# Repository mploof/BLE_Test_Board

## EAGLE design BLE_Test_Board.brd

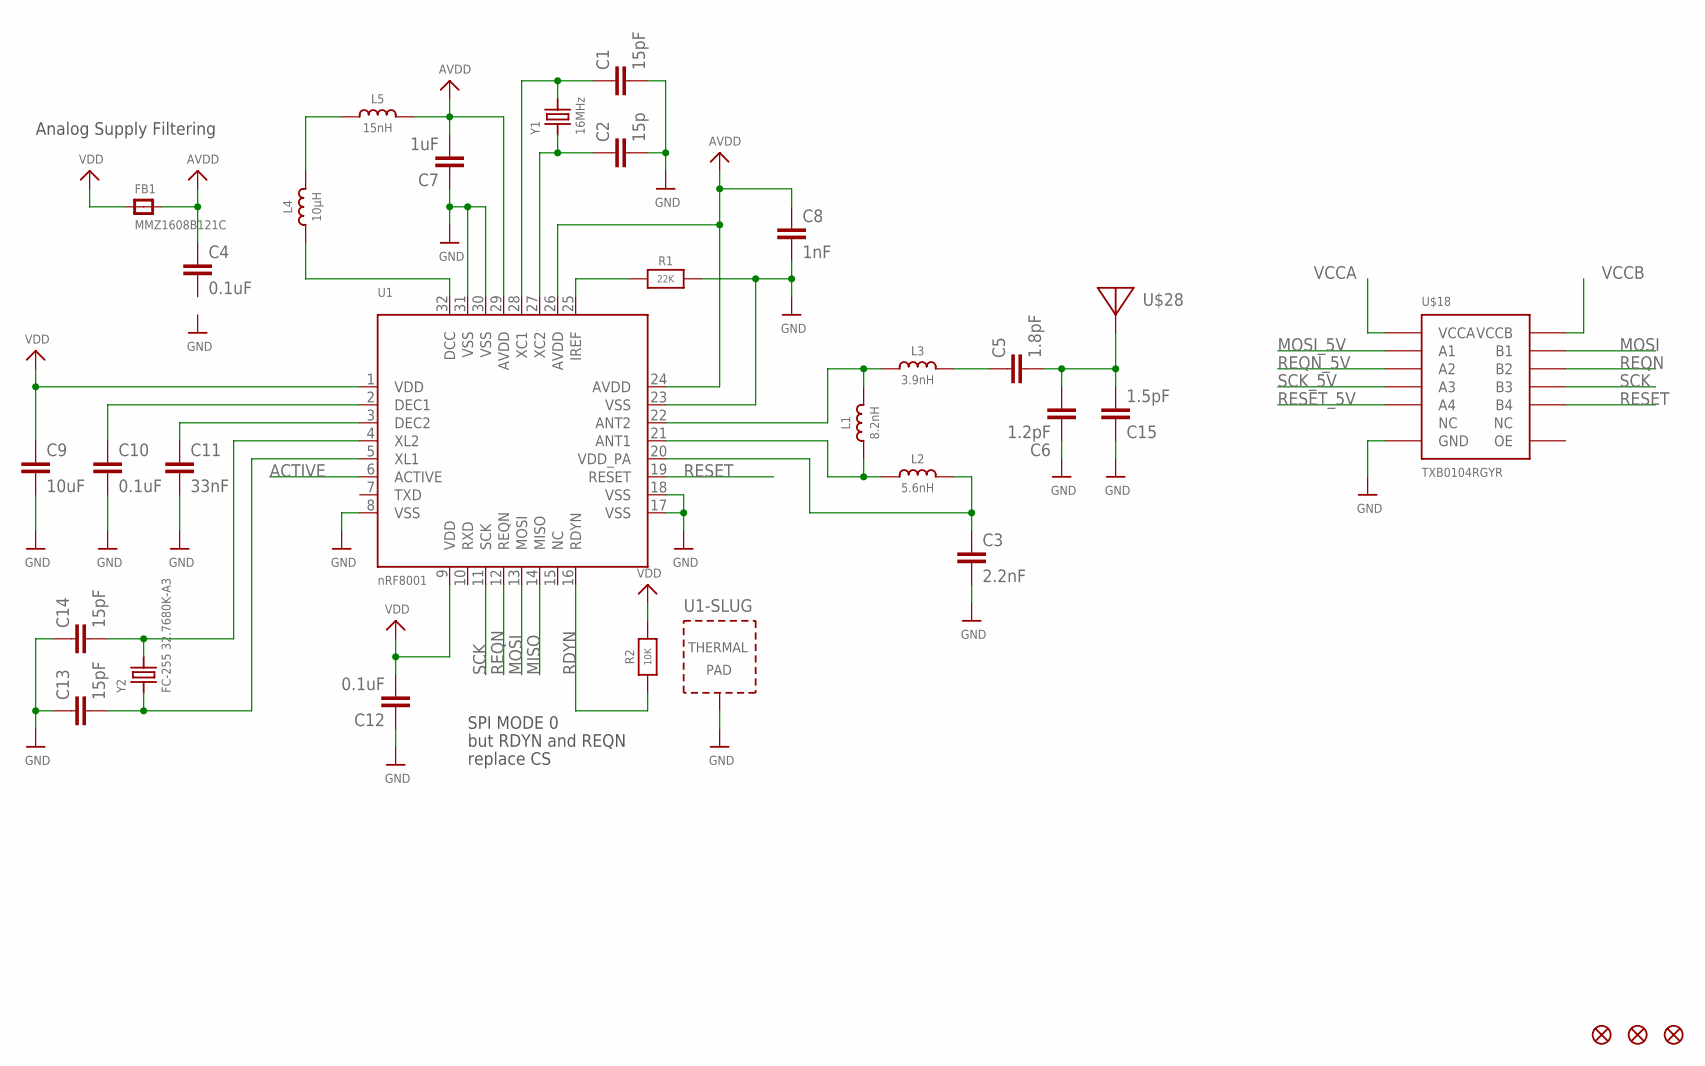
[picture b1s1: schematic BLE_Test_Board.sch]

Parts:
C1, C13, C14: 15pF; 0402-CAP
C2: 15p; 0402-CAP
C3: 2.2nF; 0402-CAP
C4, C10, C12: 0.1uF; 0402-CAP
C5: 1.8pF; 0402-CAP
C6: 1.2pF; 0402-CAP
C7: 1uF; 0402-CAP
C8: 1nF; 0402-CAP
C9: 10uF; 0402-CAP
C11: 33nF; 0402-CAP
C15: 1.5pF; 0402-CAP
FB1: MMZ1608B121C; 0805
FID1, FID2, FID3: FIDUCIAL""; FIDUCIAL_1MM
L1: 8.2nH; _0402
L2: 5.6nH; _0402
L3: 3.9nH; _0402
L4: 10µH; _0603
L5: 15nH; _0603
R1: 22K; _0805MP
R2: 10K; 0805-NO
U1: nRF8001; QFN32_5MM
U$18: TXB0104RGYR; 14-VFQFN-EXPOSED-PAD
U$28: ANTENNA_PCBNRF8001_1.6MM; ANT_PCB_2.4GHZ_NRF8001_1.6MM_1OZ
Y1: 16MHz; CRYSTAL_2.5X2
Y2: FC-255 32.7680K-A3; CRYSTAL_4.9X1.8

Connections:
ACTIVE: U1.6 (ACTIVE)
AVDD: C4.1, C7.2, C8.1, FB1.2, L5.2, U1.24 (AVDD), U1.26 (AVDD), U1.29 (AVDD)
GND: C1.2, C2.2, C3.2, C6.1, C7.1, C8.2, C9.2, C10.2, C11.2, C12.1, C13.1, C14.1, C15.1, R1.2, U1.8 (VSS), U1.17 (VSS), U1.18 (VSS), U1.23 (VSS), U1.30 (VSS), U1.31 (VSS), U1.33 (TP), U$18.P$7 (GND)
MISO: U1.14 (MISO)
MOSI: U1.13 (MOSI), U$18.P$13 (B1)
MOSI_5V: U$18.P$2 (A1)
unnamed: L1.2, L3.1, U1.22 (ANT2)
unnamed: L1.1, L2.1, U1.21 (ANT1)
unnamed: C3.1, L2.2, U1.20 (VDD_PA)
unnamed: L4.2, L5.1
unnamed: C5.1, L3.2
unnamed: C11.1, U1.3 (DEC2)
unnamed: C10.1, U1.2 (DEC1)
unnamed: C1.1, U1.28 (XC1), Y1.3 (2)
unnamed: C2.1, U1.27 (XC2), Y1.1
unnamed: L4.1, U1.32 (DCC)
unnamed: R1.1, U1.25 (IREF)
unnamed: C5.2, C6.2, C15.2, U$28.FEED
unnamed: C14.2, U1.4 (XL2), Y2.2
unnamed: C13.2, U1.5 (XL1), Y2.1
RDYN: R2.1, U1.16 (RDYN)
REQN: U1.12 (REQN), U$18.P$12 (B2)
REQN_5V: U$18.P$3 (A2)
RESET: U1.19 (RESET), U$18.P$10 (B4)
RESET_5V: U$18.P$5 (A4)
SCK: U1.11 (SCK), U$18.P$11 (B3)
SCK_5V: U$18.P$4 (A3)
VCCA: U$18.P$1 (VCCA)
VCCB: U$18.P$14 (VCCB)
VDD: C9.1, C12.2, FB1.1, R2.2, U1.1 (VDD), U1.9 (VDD)

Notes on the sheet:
Analog Supply Filtering
SPI MODE 0
but RDYN and REQN
replace CS

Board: 2 copper layers, 32 parts (1 on the bottom side), 22 nets, no tracks yet.

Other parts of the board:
U$22: ADAFRUIT_TEXT_20MM

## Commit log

2016-08-25 :tada: Added .gitattributes & .gitignore files

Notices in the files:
parts and their libraries:
microbuilder: This work is placed in the public domain, and may be freely used for commercial and non-commercial work with the following conditions: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
SparkFun-Passives: Licensing: Creative Commons ShareAlike 4.0 International - https://creativecommons.org/licenses/by-sa/4.0
